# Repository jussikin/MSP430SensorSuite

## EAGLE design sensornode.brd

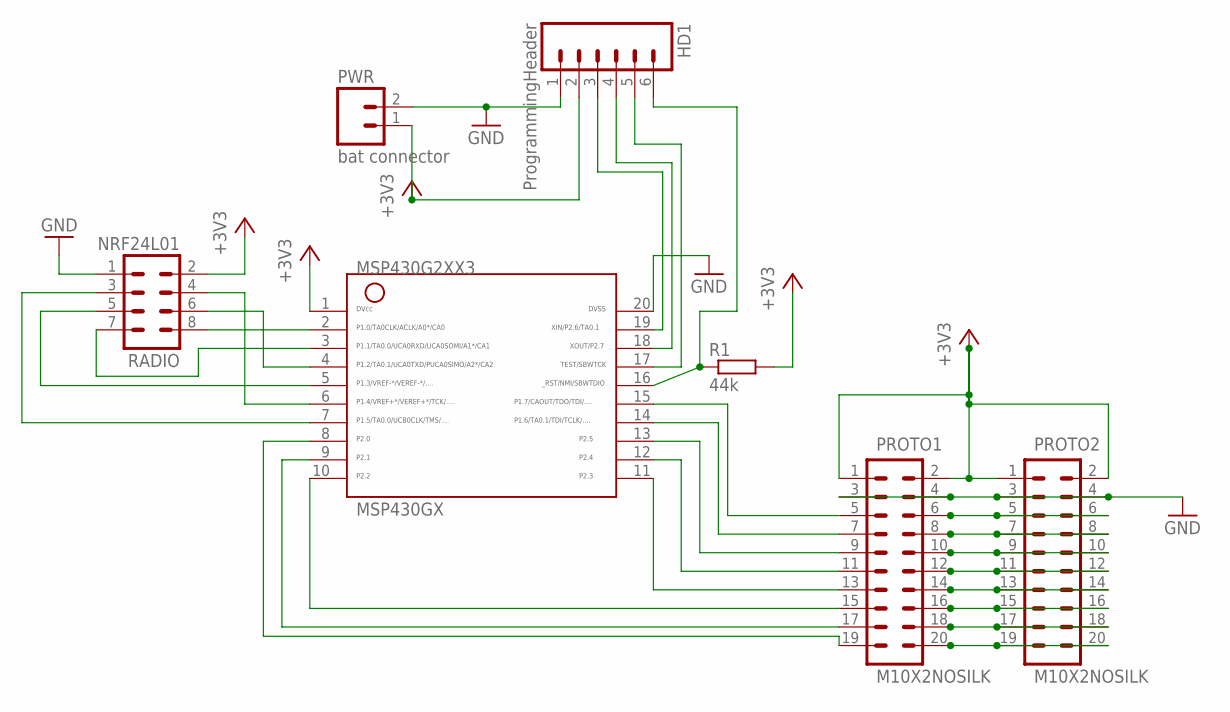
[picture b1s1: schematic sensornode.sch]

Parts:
HD1: ProgrammingHeader; 1X06
MSP430GX: G2XX3---N20; N20
PROTO1, PROTO2: M10X2NOSILK; 2X10_NOSILK
PWR: bat connector; SCREWTERMINAL-5MM-2
R1: 44k; 0207/10
RADIO: NRF24L01; MA04-2

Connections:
+3V3: HD1.2, MSP430GX.1, PROTO1.1, PROTO1.2, PROTO2.1, PROTO2.2, PWR.1, R1.2, RADIO.2
GND: HD1.1, MSP430GX.20, PROTO1.3, PROTO1.4, PROTO2.3, PROTO2.4, PWR.2, RADIO.1
unnamed: MSP430GX.6, RADIO.4
unnamed: HD1.6, MSP430GX.16, R1.1
unnamed: HD1.3, MSP430GX.19
unnamed: MSP430GX.7, RADIO.3
unnamed: MSP430GX.8, PROTO1.19
unnamed: MSP430GX.5, RADIO.5
unnamed: MSP430GX.4, RADIO.6
unnamed: MSP430GX.3, RADIO.7
unnamed: MSP430GX.9, PROTO1.17
unnamed: MSP430GX.10, PROTO1.15
unnamed: MSP430GX.11, PROTO1.13
unnamed: MSP430GX.12, PROTO1.11
unnamed: MSP430GX.13, PROTO1.9
unnamed: MSP430GX.14, PROTO1.7
unnamed: MSP430GX.15, PROTO1.5
unnamed: MSP430GX.2, RADIO.8
unnamed: HD1.4, MSP430GX.18
unnamed: HD1.5, MSP430GX.17
unnamed: PROTO1.6, PROTO2.5, PROTO2.6
unnamed: PROTO1.8, PROTO2.7, PROTO2.8
unnamed: PROTO1.10, PROTO2.9, PROTO2.10
unnamed: PROTO1.12, PROTO2.11, PROTO2.12
unnamed: PROTO1.14, PROTO2.13, PROTO2.14
unnamed: PROTO1.16, PROTO2.15, PROTO2.16
unnamed: PROTO1.18, PROTO2.17, PROTO2.18
unnamed: PROTO1.20, PROTO2.19, PROTO2.20

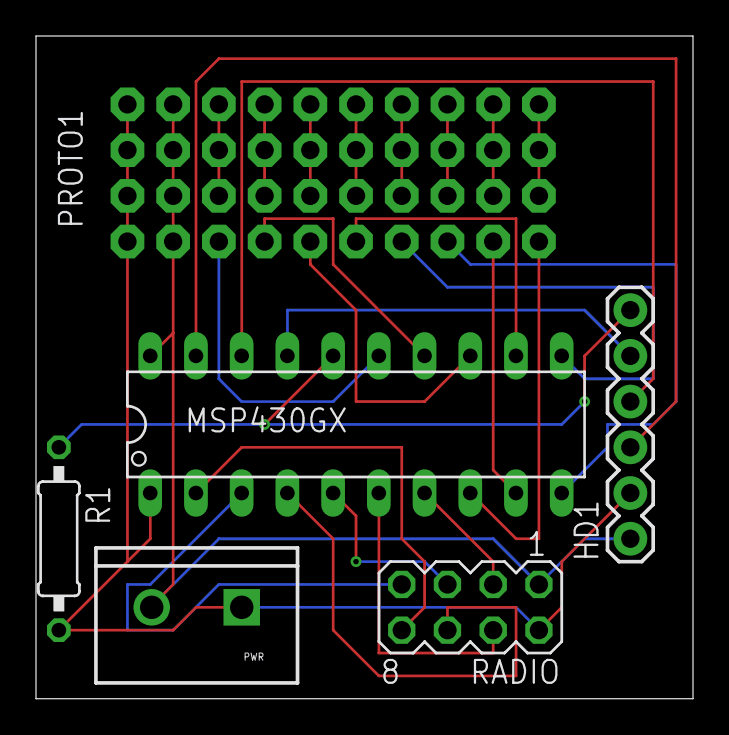
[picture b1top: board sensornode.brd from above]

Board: 2 copper layers, 36.5 x 36.8 mm, 7 parts (0 on the bottom side), 28 nets.

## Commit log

2016-06-05 Removed object files from the output

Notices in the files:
parts and their libraries:
SparkFun-Connectors: Licensing: CC v3.0 Share-Alike You are welcome to use this library for commercial purposes.
